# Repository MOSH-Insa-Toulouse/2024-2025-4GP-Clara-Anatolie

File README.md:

# 2024-2025 : Projet de capteur low-tech en graphite - Anatolie Blanc & Clara Jeandenans

## SOMMAIRE

- [SOMMAIRE](#sommaire)
- [Contexte](#contexte)
- [Livrables](#livrables)
- [Matériel nécessaire](#matériel-nécessaire)
- [Simulation électronique du capteur sous LTSpice](#simulation-électronique-du-capteur-sous-ltspice)
- [Design du PCB sous KiCad](#design-du-pcb-sous-kicad)
- [Réalisation du shield](#réalisation-du-shield)
- [Code Arduino](#code-arduino)
- [Tentatives de résolution des problèmes](#tentatives-de-résolution-des-problèmes)
- [Application Android](#application-android)
- [Banc de test](#banc-de-test)
- [Datasheet](#datasheet)
- [Conclusions et analyse critique du projet](#conclusions-et-analyse-critique-du-projet)
- [Contacts](#contacts)

## Contexte

&nbsp;&nbsp;&nbsp;&nbsp;&nbsp;&nbsp;Dans le cadre de l'UF "Du capteur au banc de test" effectué en 4ème année au département du Génie Physique de l’INSA Toulouse, nous avons développé un dispositif permettant de mesurer la contrainte appliquée sur un capteur graphite. Ce dernier est basé sur l'article "Pencil Drawn Strain Gauges and Chemiresistors on Paper" (Cheng-Wei Lin*, Zhibo Zhao*, Jaemyung Kim & Jiaxing Huang). Il est simplement composé d'un bout de papier sur lequel on vient déposer du graphite à l'aide d'un crayon à papier. La couche de graphite est constituée de particules reliées entre elles. En déformant le papier, la disposition des particules varie. En fonction du sens de flexion du papier, la déformation peut être soit une traction soit une compression. Dans le cas d’une traction, les particules de graphique s’écartent, la résistance augmente. Dans le cas d’une compression, les particules se rapprochent et la résistance diminue. Ainsi donc, ce système granulaire subit une modification de résistance et de conductance selon la contrainte exercée. Grâce à cela, nous pouvons remonter à la déformation, telle une jauge de contrainte traditionnelle.

Afin de réaliser ce dispositif permettant la mesure de déformation à partir d'un capteur low-tech, il nous faut suivre différentes étapes : simulations électroniques, design du PCB, code arduino et réalisation de la datasheet.

Ici, nous faisons un point de tout ce qui a été fait dans le cadre de ce projet.

## Livrables

Plusieurs livrables sont attendus :

- **Un shield PCB connecté à une carte arduino UNO** avec différents composants : un capteur graphite, un amplificateur transimpédance, un module bluetooth, un écran OLED, un flex sensor commercial, un potentiomètre digital, un encodeur rotatoire. D'autres composants peuvent être implémentés. Nous avons opté pour l'ajout d'un servo motor ;
- **Un code arduino** qui gère les différents composants cités précédemments (mesures de contraintes, échanges bluetooth et OLED, potentiomètre digital et boutons) ;
- **Une application Android** (sous MIT App Inventor) interfaçant le PCB et le code Arduino correspondant;
- **Une datasheet du capteur** reprenant toutes ses caractéristiques ainsi que ses tests.

## Matériel nécessaire

Afin de réaliser notre dispositif électronique, nous avons eu besoin de :

*Pour le montage amplificateur transimpédance :*

- Résistances : une de 1 kΩ, une de 10 kΩ et deux de 100 kΩ - une troisième de 100 kΩ peut être prévue, mais peut aussi être substituée par une résistance variable (le potentiomètre digital), choix que l'on a fait ;
- Potentiomètre digital MCP41050 et son support ;
- Amplificateur opérationnel LTC1050 et son support ;
- Capacités : trois de 100 nF et une de 1 μF.

*Pour le reste du dispositif :*

- Arduino Uno et son câble d’alimentation ;
- Résistance : une de 47kΩ pour le flex sensor ;
- Module Bluetooth HC05 ;
- Ecran OLED de dimension 128*64 ;
- Flex sensor ;
- Servo motor ;
- Encodeur rotatoire ;
- Capteur graphite et 2 pinces crocodiles ;
- 20 sockets ;
- 35 headers.

## Simulation électronique du capteur sous LTSpice

&nbsp;&nbsp;&nbsp;&nbsp;&nbsp;&nbsp;Notre capteur de graphite possède une résistance variable de l'ordre du gigaohm. Le courant généré, lorsque l'on applique une tension de 5V aux bornes du capteur, est très faible (de l'ordre de la dizaine de nanoampères). Ainsi, pour récupérer et pouvoir analyser ce signal, nous devons d’abord l'amplifier. C'est pourquoi nous avons utilisé un montage transimpédance, constitué d'un amplificateur opérationnel (AOP) pour fournir un signal en tension suffisant au convertisseur analogique-numérique (ADC) d'une carte Arduino UNO.

***Description du montage amplificateur transimpédance***

Nous avons testé ce montage sur le logiciel LTspice :

Pour construire ce montage, nous nous sommes basées sur ce schéma ci :

Concernant le choix de notre AOP, celui-ci devait être capable d'accepter en entrée un très faible courant. Il doit également avoir un offset de tension très faible afin de ne pas fausser les valeurs de tension transmises à l'ADC, puis analysées. Ainsi, nous avons choisi l’AOP nommé LTC 1050.

A ce circuit amplificateur, nous avons ajouté trois filtres pour améliorer notre signal :

- à l'entrée, un filtre passe-bas passif (R5,C1) ayant une fréquence de coupure de 16 Hz. Il permet de filtrer les bruits en courant sur le signal sortant du capteur ;
- un deuxième filtre passe-bas ayant une fréquence de coupure de 1.6 Hz (R3,C4) couplé à l'AOP. Ce filtre actif permet de filtrer la composante du bruit à 50 Hz provenant du réseau électrique ;
- à la sortie de l'amplificateur, un dernier filtre (R6,C2) ayant une fréquence de coupure de 1.6 kHz et permettant de filtrer le bruit lié au traitement opéré par l'amplificateur (bruits des alimentation, de l'horloge, etc...).

De plus, nous avons placé la capacité C3 de sorte à ce qu'elle filtre le bruit de l'alimentation. La résistance R5 en entrée, en plus de former avec la capacité C1 un filtre éliminant les bruits en tension, protège l'AOP contre les décharges électrostatiques. La résistance R1 sert de résistance de shunt entre la source de courant et la masse. La résistance R2 sera remplacé plus tard par un potentiomètre digital afin de régler le gain de l’AOP en fonction de nos besoins.

***Simulations réalisées sous LTSpice***

Pour savoir si nos filtres étaient efficients, nous avons testé notre circuit le logiciel LTSpice, en deux temps.
D'abord, nous avons effectué une première simulation en régime transitoire pour vérifier que l'amplification soit bien effective. Voici la réponse obtenue :

Comme on peut le constater sur le graphe, le signal est bien amplifié à 1 V. L'Arduino pourra donc l'interpréter.

Ensuite, nous avons effectué une seconde simulation, afin d'observer la réponse à un courant alternatif et ainsi de vérifier que le signal est bien filtré.

Comme on peut le constater ci-dessous, le signal paraît être filtré successivement par les 3 filtres. Le bruit est atténué d’environ 72dB à 50Hz. Le montage est performant.

## Design du PCB sous KiCad

&nbsp;&nbsp;&nbsp;&nbsp;&nbsp;&nbsp;Afin de réaliser notre PCB, nous avons reproduit le circuit précédent sur Kicad 9.0. Nous avons remplacé la résistance R2 par un potentiomètre numérique afin de pouvoir faire varier le gain de notre AOP. De plus, nous avons rajouté divers composants afin de pouvoir mesurer efficacement la valeur de notre capteur graphite et comparer les résultats obtenus :

- un flexsensor servant de témoin, afin de pouvoir comparer nos mesures avec celle du capteur graphite
- un module bluetooth HC-05 afin de pouvoir communiquer avec notre circuit depuis notre téléphone depuis une application mobile que avons codée nous-même
- un écran OLED ainsi qu’un encodeur rotatoire pour pouvoir visualiser le résultat de nos mesures et pouvoir naviguer simplement dans les différents menus servant à réaliser diverses mesures
- un servomotor.

Tous nos composants ont été installés sur un shield d'Arduino UNO.

Nous avons débuté par la création d'une librairie de symboles comportant tous les différents composants. Puis, nous avons procédé à la réalisation de la schématique électrique de l'ensemble du montage sur Kicad. Voici le schéma électrique de l'ensemble de notre montage :

Nous avons ensuite réalisé les empreintes de nos composants en respectant certaines dimensions, en vue de l'impression du PCB (diamètre des trous, forme des empreintes, etc.).Nous sommes ensuite passées à la disposition des composants sur le PCB : une étape complexe car il faut faire des compromis afin d'obtenir le placement le plus efficace (en considérant les connexions entre composants, en évitant d'avoir recours aux vias, etc.). L'image ci-dessous correspond au résultat final de notre PCB :

Nous avons aussi fait en sorte que les composants ne se touchent pas à l’aide du rendu 3D que voici :

Les fichiers KiCad sont disponibles dans le dossier [KiCad](https://github.com/MOSH-Insa-Toulouse/2024-2025-4GP-Clara-Anatolie/tree/3c948c7d110ff542ae939aa06793f8daed436087/KiCad/projet_capteur_lebon%20-%20VERSION%203)

## Réalisation du shield

&nbsp;&nbsp;&nbsp;&nbsp;&nbsp;&nbsp;Une fois notre PCB réalisé sur Kicad, nous avons pu passer à la réalisation physique de notre PCB. Voici les étapes de fabrication réalisées, avec l'aide de Cathy Crouzet (un grand merci à elle qui a pris le temps de tirer notre PCB et nous expliquer le processus de fabrication !) :

- Étape 0 (importante !) : vérification du PCB sous KiCad ;

- Étape 1 : édition du masque de gravure de notre PCB sous KiCad ;

- Étape 2 : insolation UV d'une plaquette d'époxy recouverte d'une couche de cuivre et de résine photosensible ;

- Étape 3 : immersion de la plaquette dans un révélateur afin d'éliminer la résine non-insolée ;

- Étape 4 : immersion de la plaquette dans du perchlorure de fer pour graver les pistes ;

- Étape 5 : nettoyage de la plaquette avec de l'acétone pour retirer la résine restante.

Nous avons ensuite pu réaliser le perçage de notre plaquette et y souder nos divers composants selon le schéma du PCB obtenu sur Kicad.

Voici le résultat final de notre PCB :

L’assemblage de la plaquette et l’Arduino a été plus compliqué que prévu. En effet, l'ensemble de nos trous étaient légèrement décalés les uns par rapport aux autres. Le problème semblait venir de l’étape de perçage.

De plus, le header connecté à la pin A0, qui devait servir pour le capteur de graphite, ne fonctionne pas. Nous avons donc décidé d'utiliser la pin A1, qui servira donc à récupérer les données du flex sensor et du capteur de graphite. Il nous suffit alors de brancher/débrancher les capteurs pour les échanger. Malheureusement, le signal provenant du capteur de graphite ne sera donc pas filtré et amplifié.

## Code Arduino

&nbsp;&nbsp;&nbsp;&nbsp;&nbsp;&nbsp;Nous avons utilisé l'IDE Arduino 2.3.4 . Plusieurs fichiers de test sont disponibles dans le [dossier Arduino](https://github.com/MOSH-Insa-Toulouse/2024-2025-4GP-Clara-Anatolie/tree/main/Code%20Arduino/Codes_Arduino_Tests).

Pour le [fichier principal](https://github.com/MOSH-Insa-Toulouse/2024-2025-4GP-Clara-Anatolie/tree/main/Code%20Arduino/Projet_capteur), nous avions prévu de faire une calibration du potentiomètre digital en fonction de la valeur mesurée par le capteur graphite. Ensuite, le menu de l'écran OLED propose 3 options :
- Utiliser le flex sensor
- Utiliser le capteur graphite
- Utiliser le Servo moteur

Le choix se fait grâce à l'encodeur rotatoire. En tournant, on peut passer sur les différentes options puis en sélectionner une en appuyant sur l'encodeur. Cet appui sert également à sortir du menu selectionné.

L'option concernant le flex sensor récupère sa valeur et l'écrit sur l'OLED. L'option "Graphite Sensor" récupère sa valeur de résistance et l'affiche aussi sur l'écran. Enfin, la dernière option déplace le servo moteur en fonction de la valeur du flex sensor.

Le calcul de la résistance du capteur en graphite se fait avec la formule : $Res=R1*(1+\frac{R3}{R2})*\frac{Vcc}{Vadc}-R1-R5$

Dans notre cas, la résistance R2 est variable : c'est celle du potentiomètre digital qui est calculé avec : $R2=\frac{47500*pos}{256}+125$, où $47500$ correspond à la valeur de résistance maximale de notre MCP41050 et $pos$ la position du potentiomètre parmi les 256 valeurs.

Le module bluetooth HC-05 reçoit également les valeurs du capteur graphite et affiche un graphe.

## Tentatives de résolution des problèmes

&nbsp;&nbsp;&nbsp;&nbsp;&nbsp;&nbsp;Lorsque nous tentons de récupérer la valeur de la résistance du capteur graphite, nous obtenons une valeur infinie. En effet, la tension de sortie de ce capteur est nulle. Nous avons vérifié toutes les connexions sur le PCB à l'aide d'un multimètre. Nous avons également vérifié les valeurs des résistances et changé les composants. Nous avons aussi essayé de remplacer le potentiomètre par une résistance fixe de 1 kOhms, le capteur graphite par une résistance fixe de 100 MOhm et le PCB par une breadboard. Enfin, nous avons essayé diférents programmes, qui donnaient tous le meme resultat. Nous n'avons pas réussi à identifier le problème et nous avions déjà passé beaucoup de temps dessus alors nous  avons décidé d'utiliser le pin A1, celui du flex sensor, pour récupérer les valeurs du capteur graphite.

## Application Android

Une application a été développée sous [MIT App Inventor](https://appinventor.mit.edu/). Elle fonctionne lorsque l'on entre dans le menu "Flex Sensor", sur le menu principal. Nous avons mis un bouton permettant de sélectionner l'appareil connecté au bluetooth, une zone de lecture de la valeur de la résistance mesurée, ainsi qu'un graphe permettant de voir l'évolution temporelle de cette valeur. Un dernier bouton permet d'écrire la valeur 10 dans le serial monitor, afin de tester l'envoi de données de l'application vers le dispositif bluetooth. Nous n'avons malheureusement pas eu le temps de développer plus l'application, souhaitant résoudre le problème du capteur graphite.

L'interface utilisateur de l'application :

La face arrière de l'application :

Un test réalisé avec le flex sensor :

Le QR code pour télécharger l'application : 

## Banc de test

&nbsp;&nbsp;&nbsp;&nbsp;&nbsp;&nbsp;Pour caractériser notre capteur et son montage, nous avons décidé d'utiliser des demi-cercles avec des rayons de courbure différents. Grâce à ces demi-cercles, nous avons pu calculer la variation de la résistance électrique $\frac{\Delta R}{R_0}$ en fonction de la déformation $\epsilon=\frac{e}{D}$. Nous avons ici mesuré notre épaisseur de notre papier e = 0.2 mm.

Voici les courbes obtenues :

Nous remarquons que la résistance augmente lorsque l'on met le capteur en tension et qu'elle diminue lors de la compression. En tension, la distance entre les atomes augmente et la résistance augmente avec. Le contraire se produit pour la compression.

En fonction du type de crayon utilisé, les variations relatives de résistance changent. Plus le crayon est gras (2H->H->HB->B->2B avec 2B contenant le plus de carbone), moins sa variation relative de résistance est élevée.

Enfin, on peut comparer notre capteur avec un flex sensor commercial. Il semblerait que le flex sensor soit plus sensible à la déformation, en plus d'être plus solide pour des déformations importantes. Cepndant, le capteur graphite a un nombre d'utilisation très limité.

De plus, nos mesures ne sont pas forcément reproductibles car elles dépendent fortement de la quantité de crayon déposé. Ainsi, la résistance varie beaucoup d'un capteur à un l'autre.

## Datasheet

La datasheet de notre capteur est disponible [ici](Datasheet).

## Conclusions et analyse critique du projet

&nbsp;&nbsp;&nbsp;&nbsp;&nbsp;&nbsp;Ce projet a été très enrichissant. En menant un projet de bout en bout, des simulations à la datasheet, nous avons pu avoir un avant goût du travail d'ingénieur. Nous avons aussi pu avoir une vision des nombreuses compétences (simulation électronique, développement informatique, design d'un montage électronique, fabrication physique de ce dernier, etc.) indispensables à un ingénieur de nos jours. En ce sens, c'est un projet qui a donc été assez professionnalisant. De  plus, il est gratifiant de pouvoir fabriquer un produit dans son entièreté et de le voir fonctionner.

En ce qui concerne le capteur graphite fabriqué, il n'est malheureusement pas fonctionnel pour nous, malgré toutes nos tentatives de compréhension du problème. Les tests avec la pin du flex sensor nous permettent de dégager des tendances à peu près cohérentes avec la physique. Cependant, les conditions de tests étant rudimentaires, peu reproductibles et non flitrées dans notre cas, cela conduit à des résultats assez aléatoires. Il est donc nécessaire de prendre du recul sur leur véracité.

## Contacts

&nbsp;&nbsp;&nbsp;&nbsp;&nbsp;&nbsp;Pour toute information complémentaire, vous pouvez nous contacter à ces adresses mails :

- Anatolie Blanc : <anatolie.blanc@insa-toulouse.fr>
- Clara Jeandenans : <clara.jeandenans@insa-toulouse.fr>

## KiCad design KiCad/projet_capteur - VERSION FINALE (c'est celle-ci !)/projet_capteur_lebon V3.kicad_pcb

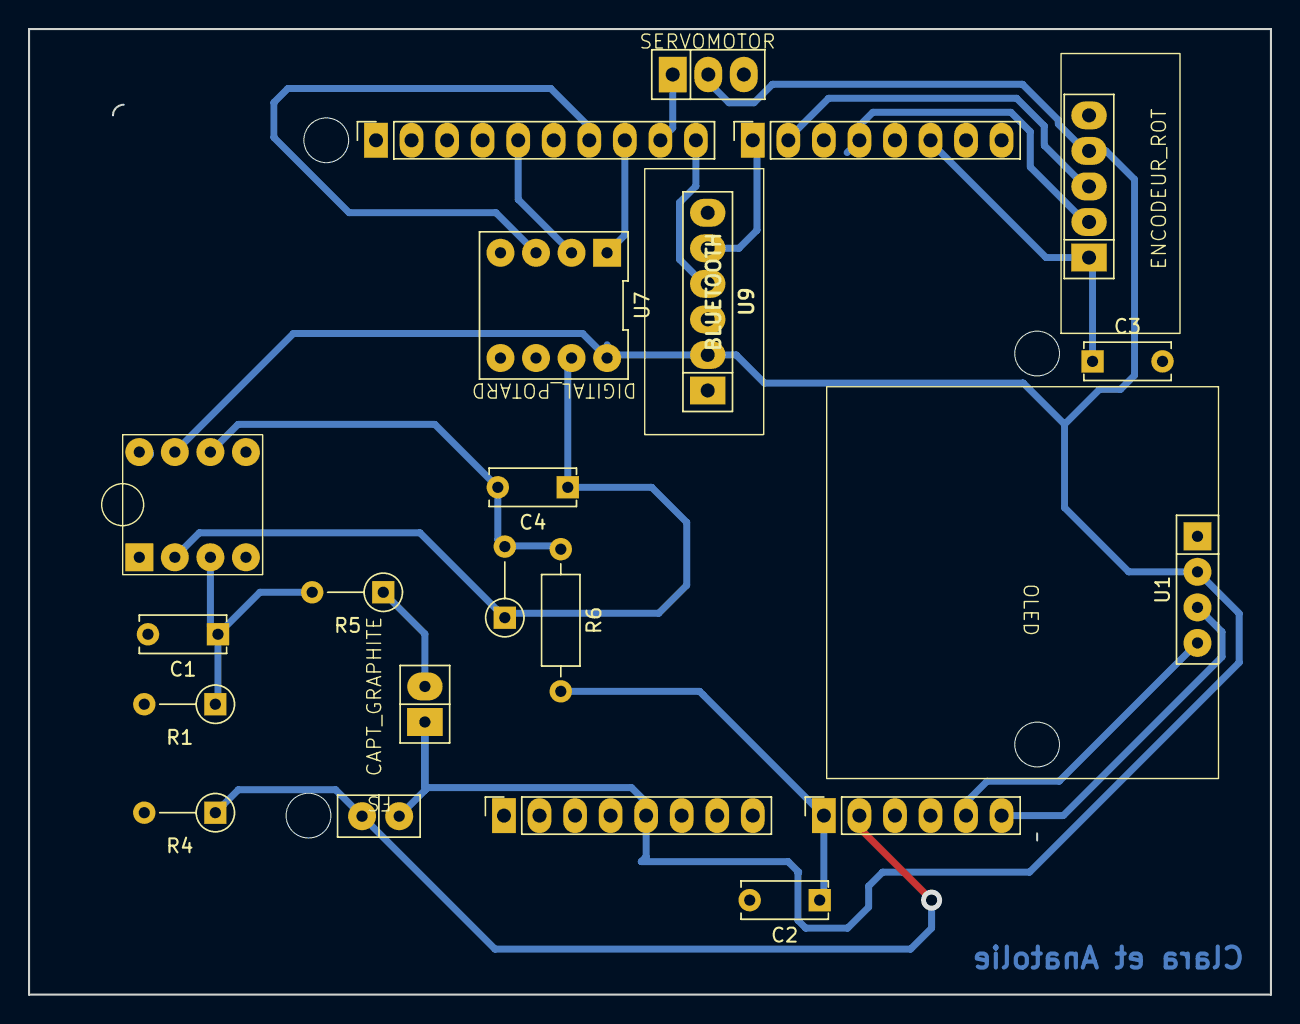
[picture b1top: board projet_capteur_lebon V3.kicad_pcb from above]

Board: 2 copper layers, 88.8 x 69.0 mm, 25 parts (0 on the bottom side), 19 nets.

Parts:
C1, C2, C3: 100n; C_Disc_D6.0mm_W2.5mm_P5.00mm
C4: 1u; C_Disc_D6.0mm_W2.5mm_P5.00mm
J1: Power; PinSocket_1x08_P2.54mm_Vertical
J2: Digital/PWM; PinSocket_1x10_P2.54mm_Vertical
J3: Analog; PinSocket_1x06_P2.54mm_Vertical
J4: Digital/PWM; PinSocket_1x08_P2.54mm_Vertical
MH1, MH2, MH3, MH4: MountingHole_3.2mm
R1, R3: 100k; R_Axial_DIN0207_L6.3mm_D2.5mm_P5.08mm_Vertical
R4: 47k; R_Axial_DIN0207_L6.3mm_D2.5mm_P5.08mm_Vertical
R5: 10k; R_Axial_DIN0207_L6.3mm_D2.5mm_P5.08mm_Vertical
R6: 1k; R_Axial_DIN0207_L6.3mm_D2.5mm_P10.16mm_Horizontal
U1: SIP-4
U2: ENCODEUR ROT
U4, U7: DIP-8_296
U5: SIP-2
U6: SIP-3
U8: CAPTEUR_GRAPHITE
U9: BLUETOOTH

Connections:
5V: J1.5, U1.2 (VCC), U2.4 (VCC), U4.7 (VCC+), U5.1 (Vcc), U6.2 (VCC), U7.8 (VCC), U8.1 (VCC), U9.2 (VCC)
/13: J2.5, U7.2 (SCK)
/*9: J2.9, U6.1 (Data)
/*10: J2.8, U7.1 (CS)
/*11: J2.7, U7.3 (SDI)
CAPT_AMPL: C2.1, J3.1, R6.2
CLK: C3.1, J4.6, U2.1 (CLK)
DT: J4.4, U2.2 (DT)
GND: C1.2, C2.2, C3.2, J1.6, J1.7, J2.4, R1.2, R4.2, U1.1 (GND), U2.5 (GND), U4.4 (VCC-), U6.3 (GND), U7.4 (GND), U7.5 (POA), U7.6 (POW), U9.3 (GND)
unnamed: C1.1, R1.1, R5.2, U4.3 (IN+)
unnamed: C4.2, R3.2, R6.1, U4.6 (OUT)
OUT_CAPT: R5.1, U8.2 (OUT_CAPT)
OUT_FLEX: J3.2, R4.1, U5.2 (Out)
R2: C4.1, R3.1, U4.2 (IN-), U7.7 (POB)
RX: J4.1, U9.5 (RX)
SCL: J2.1, J3.6, U1.3 (SCL)
SDA: J2.2, J3.5, U1.4 (SDA)
SW: J4.2, U2.3 (SW)
TXD: J2.10, U9.4 (TXD)

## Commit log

2025-03-17 new repository sur mosh insa
2025-03-17 ajout mit appli
2025-03-17 version 2
2025-03-19 version 3 en cours
2025-03-19 fin V3
2025-03-19 version finale validee par cathy qui sera imprimee
2025-03-25 init code arduino
2025-03-25 servo et encodeur arduino
2025-03-28 avancement code
2025-04-02 ajout lib encodeur
2025-04-02 bonne librairie pr encodeur
2025-04-02 ajout codes arduino cours et avancement code
2025-04-07 jsp ce que c'est mais j'ai ça
2025-04-07 creations dossier photos avec photos dedans et modif vue 3D
2025-04-07 readme mais pas fini
2025-04-07 avancement code menu oled
2025-04-08 avancement code menu oled + pb encodeur
2025-04-09 avancement code encodeur mais tjrs pb
2025-04-09 améliorations readme
2025-04-09 signature
2025-04-11 avancement code 11/04
2025-04-14 ajout readme et test bench recup
2025-04-14 ajout readme et recup tests bench
2025-04-15 arduino avancées
2025-04-15 resolution pb menu affichage
2025-04-21 bluetooth et android débuts
2025-05-06 trucs
2025-05-06 Finitions README + avançement code
2025-05-06 code pour banc de test
2025-05-08 ajout mesures
2025-05-08 correction readme
2025-05-13 ajt servo + debut com
2025-05-18 fin commentaires
2025-05-18 avancement readme + fin arduino
2025-05-18 avancement readme
2025-05-18 photo
2025-05-18 avancement readme encore
2025-05-19 correction dtostrf code
2025-05-19 fin code avec servo
2025-05-19 fin code
2025-05-19 ajout datasheet + mise en forme git
2025-05-19 readme
2025-05-19 readme encore
2025-05-19 re read me g fini
2025-05-21 bebe modifs readme
2025-05-21 tendances lin sur courbes datasheet
2025-05-21 lien datasheet readme
2025-05-21 excel banc de test jsp quoi
2025-05-22 android sur readme
2025-05-22 bebe corrections readme
2025-05-22 rangement photos
2025-05-22 encore un peu rangement
2025-05-28 détails finaux code
2025-05-28 dernieres modifs
2025-05-28 images readme
